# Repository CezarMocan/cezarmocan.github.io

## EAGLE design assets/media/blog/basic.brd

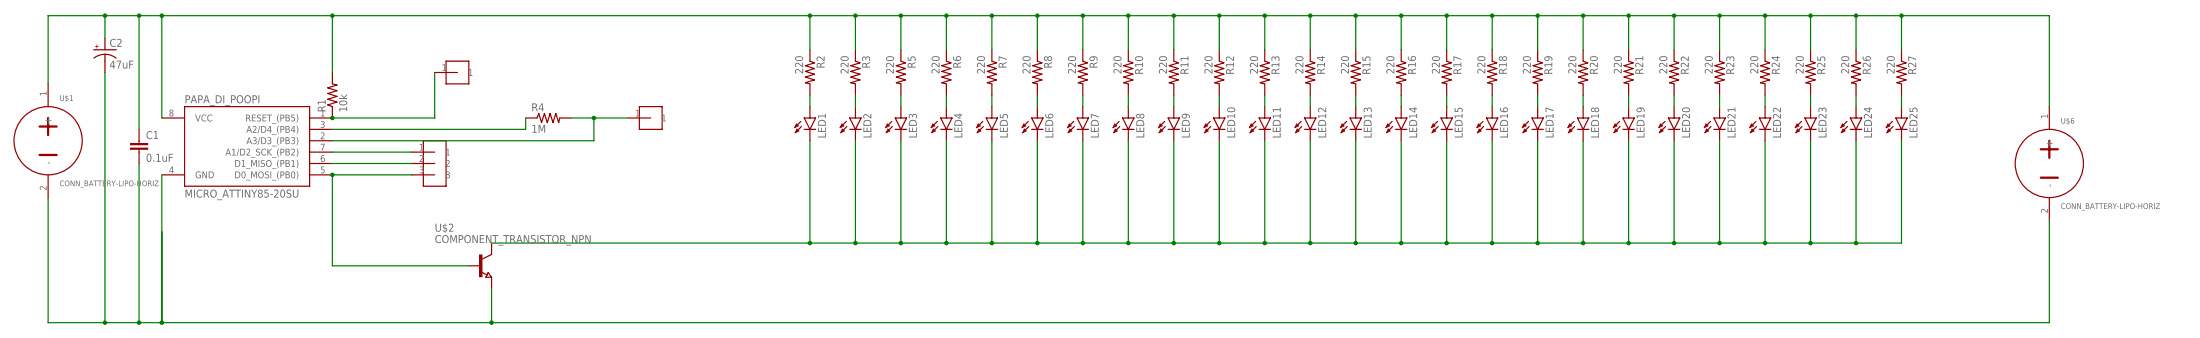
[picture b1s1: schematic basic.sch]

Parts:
C1: 0.1uF; 0805
C2: 47uF; CAP_RADIAL_CAN_10MM
CAP_SENSOR_1, CAP_SENSOR_2: HEADER-1-TESTPOINT; TESTPOINT-1
LED1, LED2, LED3, LED4, LED5, LED6, LED7, LED8, LED9, LED10, LED11, LED12, LED13, LED14, LED15, LED16, LED17, LED18, LED19, LED20, LED21, LED22, LED23, LED24, LED25: LED-0805; CHIP-LED0805
PAPA_DI_POOPI: MICRO_ATTINY85-20SU; SOIC8
R1: 10k; 0805
R2, R3, R5, R6, R7, R8, R9, R10, R11, R12, R13, R14, R15, R16, R17, R18, R19, R20, R21, R22, R23, R24, R25, R26, R27: 220; 0805
R4: 1M; 0805
U$1, U$6: CONN_BATTERY-LIPO-HORIZ; JST-PH-2-SMT-RA
U$2: COMPONENT_TRANSISTOR_NPN; SOT23
U$5: HEADER-3-TESTPOINT; TESTPOINT-3

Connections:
COLLECTOR: LED1.C, LED2.C, LED3.C, LED4.C, LED5.C, LED6.C, LED7.C, LED8.C, LED9.C, LED10.C, LED11.C, LED12.C, LED13.C, LED14.C, LED15.C, LED16.C, LED17.C, LED18.C, LED19.C, LED20.C, LED21.C, LED22.C, LED23.C, LED24.C, LED25.C, U$2.3 (C)
GND: C1.2, C2.-, PAPA_DI_POOPI.4 (GND), U$1.2 (-), U$2.2 (E), U$6.2 (-)
unnamed: CAP_SENSOR_1.1, PAPA_DI_POOPI.1 (RESET_(PB5)), R1.1
unnamed: LED3.A, R5.2
unnamed: PAPA_DI_POOPI.5 (D0_MOSI_(PB0)), U$2.1 (B), U$5.3
unnamed: PAPA_DI_POOPI.7 (A1/D2_SCK_(PB2)), U$5.1
unnamed: LED1.A, R2.2
unnamed: LED2.A, R3.2
unnamed: PAPA_DI_POOPI.3 (A2/D4_(PB4)), R4.1
unnamed: CAP_SENSOR_2.1, PAPA_DI_POOPI.2 (A3/D3_(PB3)), R4.2
unnamed: PAPA_DI_POOPI.6 (D1_MISO_(PB1)), U$5.2
unnamed: LED4.A, R6.2
unnamed: LED7.A, R9.2
unnamed: LED5.A, R7.2
unnamed: LED6.A, R8.2
unnamed: LED8.A, R10.2
unnamed: LED9.A, R11.2
unnamed: LED10.A, R12.2
unnamed: LED11.A, R13.2
unnamed: LED12.A, R14.2
unnamed: LED13.A, R15.2
unnamed: LED14.A, R16.2
unnamed: LED15.A, R17.2
unnamed: LED16.A, R18.2
unnamed: LED17.A, R19.2
unnamed: LED18.A, R20.2
unnamed: LED19.A, R21.2
unnamed: LED20.A, R22.2
unnamed: LED21.A, R23.2
unnamed: LED22.A, R24.2
unnamed: LED23.A, R25.2
unnamed: LED24.A, R26.2
unnamed: LED25.A, R27.2
POWER: C1.1, C2.+, PAPA_DI_POOPI.8 (VCC), R1.2, R2.1, R3.1, R5.1, R6.1, R7.1, R8.1, R9.1, R10.1, R11.1, R12.1, R13.1, R14.1, R15.1, R16.1, R17.1, R18.1, R19.1, R20.1, R21.1, R22.1, R23.1, R24.1, R25.1, R26.1, R27.1, U$1.1 (+), U$6.1 (+)

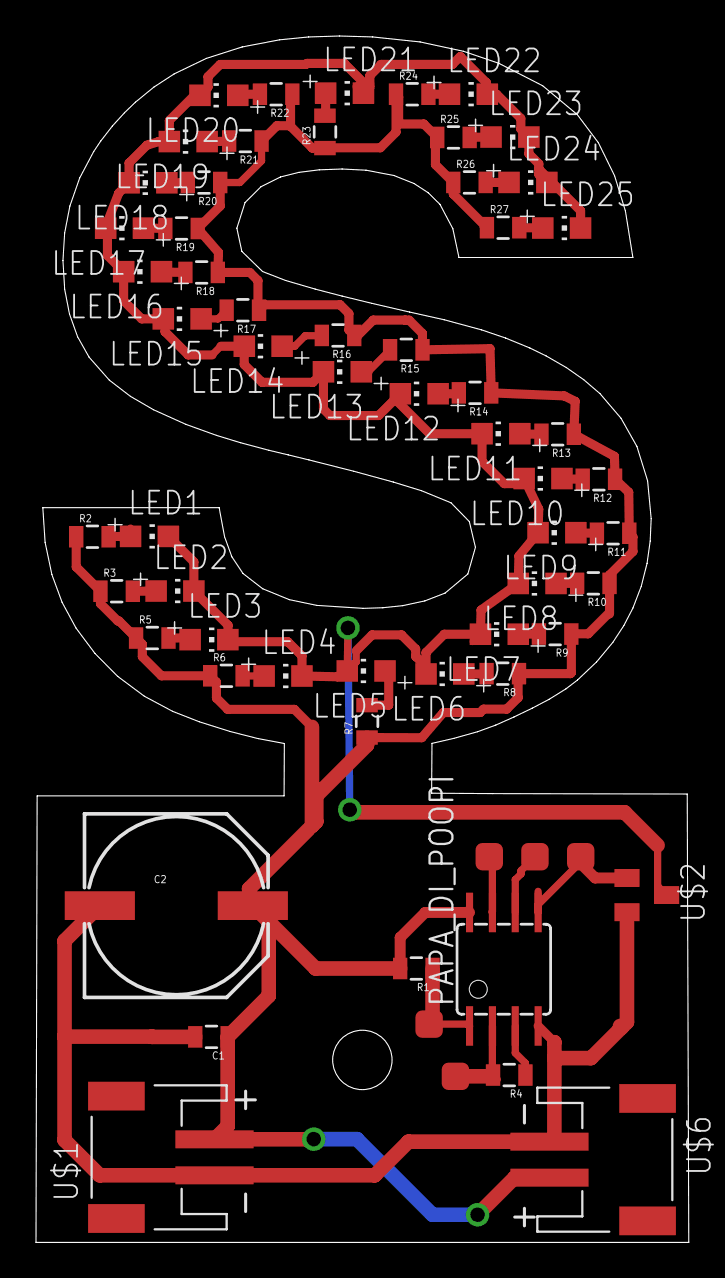
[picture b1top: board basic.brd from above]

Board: 2 copper layers, 36.3 x 67.0 mm, 61 parts (0 on the bottom side), 34 nets.

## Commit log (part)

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2018-11-30 First portfolio commit
2018-12-01 Portfolio complete
2018-12-01 Portfolio complete 2
2018-12-01 Added favicon
2018-12-01 Built
2018-12-01 test
2018-12-01 Added CNAME
2018-12-01 Added 000pen.space
2018-12-01 google analytics
2019-01-05 Added an argument for a new digital currency; small adjustments
2019-01-06 Updated documentation for algorithm4friends
2019-02-15 Updated work
2019-04-25 gakko gallery link
2019-09-02 Responsive site; updated about
2019-09-02 Added blog
2019-09-04 Blog updates
2019-09-04 Small css update
2019-09-05 version 1 type
2019-09-05 blog functional
2019-09-07 fixed font weight
2019-09-09 Added blog post
2019-09-09 Writing complete
2019-09-09 Finalized blog post
2019-09-17 Added sound walk blog post
2019-09-18 PComp blog post
2019-09-18 fixed images
2019-09-23 Sound walk reflection piece
2019-10-02 Half the post for pcomp
2019-10-02 Finished pcomp blog post
2019-10-02 added code
2019-10-10 Nether blog post complete
2019-10-10 Added images
2019-10-30 Intro fab blog post
2019-11-05 Added ghost box
2019-11-05 Added initial pcomp ideas
2019-11-05 updated assets
2019-11-06 Blog
2019-11-06 Photos
2019-11-06 fixed image names
2019-11-13 fab blog post
2019-11-22 added resume
2019-11-22 Updated resume link
2019-12-11 fab blog posts
2019-12-13 clock post
2019-12-23 Added untitled to portfolio
2019-12-23 feed
2019-12-28 added disappearing
2020-01-12 Updated with 2019 work; Updated design
2020-01-12 Responsive
2020-01-12 polish
2020-01-12 Color scheme
2020-01-12 blog styling
2020-01-20 CSS and new resume
2020-02-05 LIPP #1
2020-02-12 LIPP blog post
2020-02-14 Homemade hardware assignment
2020-02-19 lipp feb 19
2020-02-21 homemade hardware blog post
2020-02-23 Updated board design
2020-03-03 LIPP blog
2020-03-03 Date
2020-03-03 name
2020-03-13 homemade hardware final
2020-03-13 video
2020-03-27 Homemade Hardware prototype
2020-03-30 Synthetic Architectures treatment
2020-04-06 CC blog post
2020-04-06 rename
2020-04-13 Critical Comm blog post
2020-04-17 Homemade Hardware final eagle
2020-06-08 privacy policy
2020-08-19 New resume
2020-09-15 pa post
2020-09-22 PA blog post
2020-10-01 New index page
2020-10-01 Project page
2020-10-01 Transition projects
2020-10-01 Updated content
2020-10-02 More projects
2020-10-02 Webring
2020-10-02 fixed links
2020-10-02 nothing
2020-10-19 audio
2020-12-04 Small change in vimeo embed
2020-12-04 Fixed vimeo player on change project
2020-12-27 Added virtualis & declared vvvvvvoid
2020-12-28 Content updates
2020-12-29 new skin; projects
2020-12-29 reduce loading size of index page
2021-01-04 updated about page
2021-01-31 about page updates
2021-07-13 Bump addressable from 2.5.2 to 2.8.0
    Bumps [addressable](https://github.com/sporkmonger/addressable) from 2.5.2 to 2.8.0.
    - [Release notes](https://github.com/sporkmonger/addressable/releases)
    - [Changelog](https://github.com/sporkmonger/addressable/blob/main/CHANGELOG.md)
    - [Commits](https://github.com/sporkmonger/addressable/compare/addressable-2.5.2...addressable-2.8.0)
    ---
    updated-dependencies:
2021-10-09 Updated layout
2021-10-09 Aracdia project complete
2021-10-10 typo
2021-10-10 arcadia description update
2021-10-10 office olympics pics
2021-10-10 added chestnut series
2021-10-12 updated about & image for worldviews
2021-11-01 Updated arcadia inc video
2021-11-01 updated feed
2022-02-04 updated about page styling
2022-04-02 networked media backup site
2022-11-06 Portfolio updates, November 2022
2022-12-05 Updated images for delicate chaos
2023-04-10 World upstream and updates
2023-04-10 push
2023-08-09 Updated location
2023-09-17 September 2023 updates
2023-10-31 about page update
2023-11-02 Small update
2023-11-12 World Upstream video & shows
2023-12-11 Site updates
2023-12-21 Added PDF
2024-01-15 Updates for Arcadia and about page
2024-01-15 Bundle update
2024-02-17 Portfolio updates
2024-02-17 CSS fix
2024-02-17 Added missing assets
2024-02-17 Arcadia /rosa img
2024-02-17 Images for arcadia
2024-02-17 More images for World Upstream
2024-02-17 Panke photos
2024-02-17 HIG images
2024-03-20 Fixed feelings; World Upstream video & exhibition updates
2024-04-05 Plotter drawings & update about page
2024-04-05 About update
2024-08-01 Bump rexml from 3.2.5 to 3.3.3
    Bumps [rexml](https://github.com/ruby/rexml) from 3.2.5 to 3.3.3.
    - [Release notes](https://github.com/ruby/rexml/releases)
    - [Changelog](https://github.com/ruby/rexml/blob/master/NEWS.md)
    - [Commits](https://github.com/ruby/rexml/compare/v3.2.5...v3.3.3)
    ---
    updated-dependencies:
2024-08-22 Bump rexml from 3.2.5 to 3.3.6
    Bumps [rexml](https://github.com/ruby/rexml) from 3.2.5 to 3.3.6.
    - [Release notes](https://github.com/ruby/rexml/releases)
    - [Changelog](https://github.com/ruby/rexml/blob/master/NEWS.md)
    - [Commits](https://github.com/ruby/rexml/compare/v3.2.5...v3.3.6)
    ---
    updated-dependencies:
2024-10-28 Bump rexml from 3.2.5 to 3.3.9
    Bumps [rexml](https://github.com/ruby/rexml) from 3.2.5 to 3.3.9.
    - [Release notes](https://github.com/ruby/rexml/releases)
    - [Changelog](https://github.com/ruby/rexml/blob/master/NEWS.md)
    - [Commits](https://github.com/ruby/rexml/compare/v3.2.5...v3.3.9)
    ---
    updated-dependencies:
2024-12-02 assets
2024-12-15 Update schema
2025-03-05 Footer year
2025-03-14 footer lol
2025-03-27 arab bank prize page
2025-04-21 world upstream
2025-06-30 Updated exhibitions
2025-07-27 world upstream manual
2025-12-09 CV update
2026-05-28 arcadia uppdate
